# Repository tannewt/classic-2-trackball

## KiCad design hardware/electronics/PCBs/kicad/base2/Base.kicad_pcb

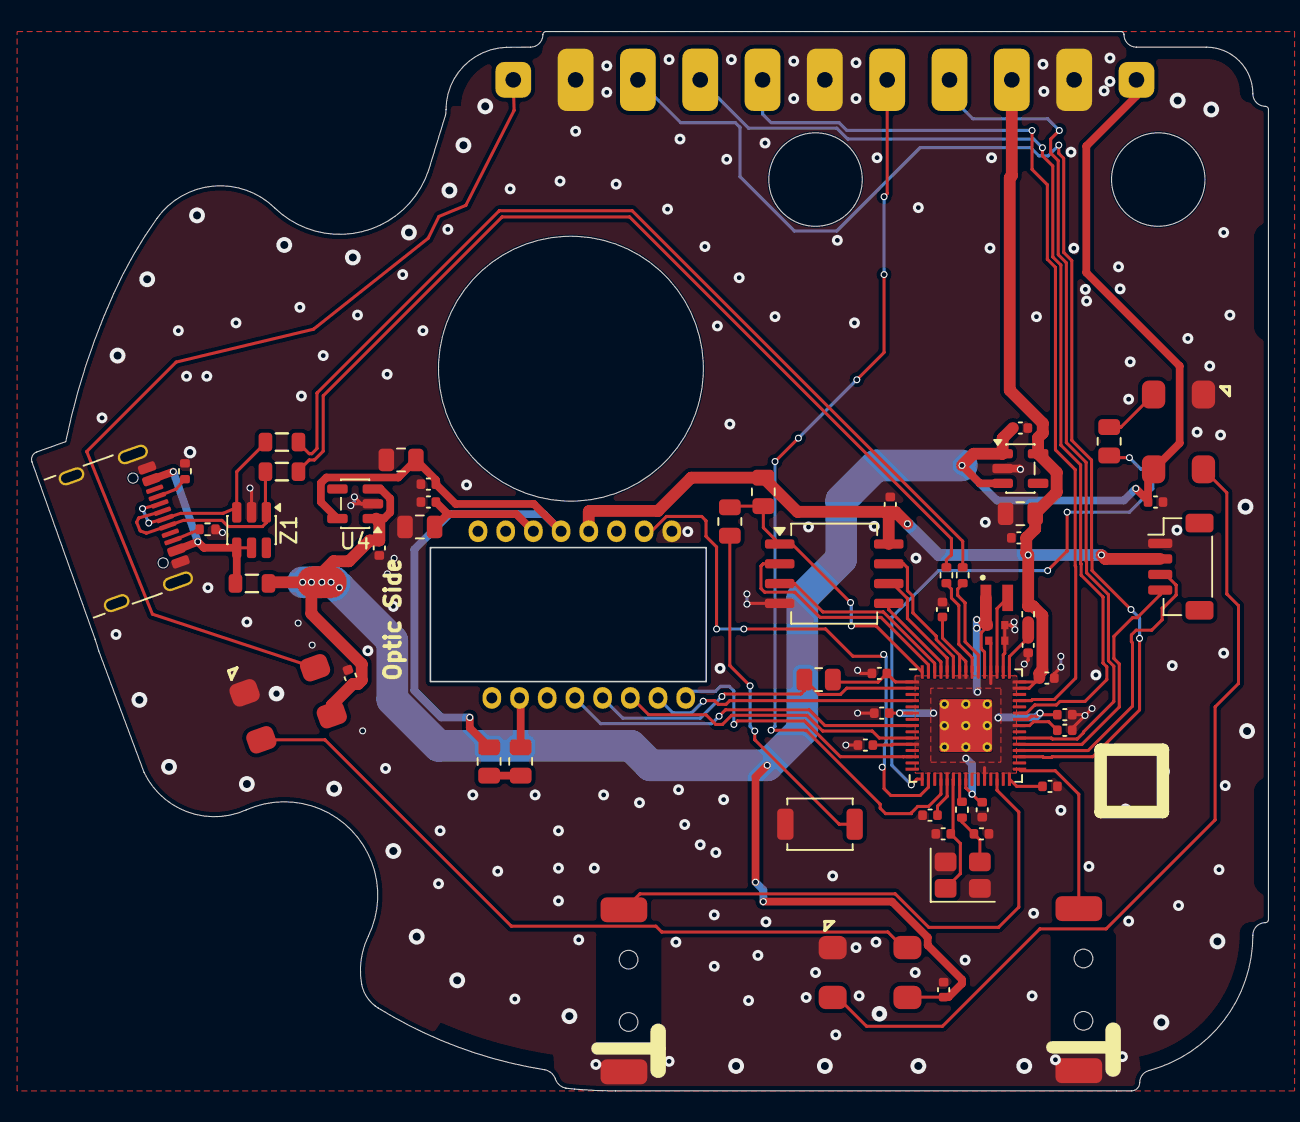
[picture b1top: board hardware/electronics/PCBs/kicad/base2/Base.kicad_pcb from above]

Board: 2 copper layers, 79.4 x 68.0 mm, 69 parts (1 on the bottom side), 49 nets.

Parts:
C1, C11, C15, C20, C23, C24, C25, C29, C30, C31, C32, C33, C34, C35: 100nF; C_0402_1005Metric
C3, C4: 15pF; C_0402_1005Metric
C10, C13, C17: 10uF; C_0805_2012Metric
C12, C14, C16, C18: 1uF; C_0402_1005Metric
C22, C28: 4.7uF; C_0402_1005Metric
C26, C27: 4.7uF; C_0402_1005Metric_small_pads
CJ1, CJ2, CJ3, CJ4, CJ5, CJ6, CJ7, CJ8, CJ9, CJ10, CJ11: PCBJointCastellationJoint; PCBJoint
D1, D3, D5: IN-PI55TATPRPGPB
FB1, FB2, FB3: GZ2012D601TF; FB_0805
J3: USB_C_Receptacle_USB2.0_16P; USB_C_Receptacle_HRO_TYPE-C-31-M-31
J14: Conn_01x04; JST_SH_BM04B-SRSS-TB_1x04-1MP_P1.00mm_Vertical
L1: AOTA-B201610S3R3-101-T; L_pol_2016
R1, R16: 1k; R_0805_2012Metric
R2, R5: 10k; R_0805_2012Metric
R3, R4: 22R; R_0805_2012Metric
R6: 33; R_0402_1005Metric
R7, R8: 27; R_0402_1005Metric
R9: 1k; R_0402_1005Metric
R10, R11: 5.1k; R_0402_1005Metric
SW1, SW2: D2LS-21
SW3: TS-1088-AR02016; SW_SPST_TS-1088-xR020
U1: W25Q16JVSSIQ; SOIC-8_5.3x6.2mm_P1.27mm
U2: PMW3360DM-T2QU
U3: AP2202K-3.3; SOT-23-5
U4: AP2204K-1.8; SOT-23-5
U6: RP2350A; RP2350-QFN-60-1EP_7x7_P0.4mm_EP3.4x3.4mm_ThermalVias
Y1: ABM8-272-T3; Crystal_SMD_3225-4Pin_3.2x2.5mm
Z1: IP4220CZ6,125; SOT-23-6

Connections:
+1V1: C15.1, C22.1, C24.1, C27.1, L1.1, U6.6 (DVDD), U6.23 (DVDD), U6.39 (DVDD), U6.50 (VREG_FB)
+3.3V: C1.2, C13.2, C14.2, C26.1, C29.1, C30.1, C31.1, C32.1, C33.1, C34.1, C35.1, CJ8.1 (1_1), J14.2, R2.1, R5.2, R6.1, U1.8 (VCC), U2.5 (VDDIO), U3.5 (VOUT), U6.1 (IOVDD), U6.11 (IOVDD), U6.20 (IOVDD), U6.26 (RUN), U6.30 (IOVDD), U6.38 (IOVDD), U6.44 (ADC_AVDD), U6.45 (IOVDD), U6.49 (VREG_VIN), U6.53 (USB_OTP_VDD), U6.54 (QSPI_IOVDD)
/LBS/ButtonLittleFinger: SW2.B, U6.31 (GPIO19)
/LBS/ButtonRingFinger: SW1.B, U6.28 (GPIO17)
/LED/LEDData: R16.2, U6.16 (GPIO12)
/LED/LEDDataOut: CJ10.1 (1_1), D5.2 (DOUT)
/LED/V_USB: C12.2, C16.2, C20.2, C23.2, C25.2, CJ11.1 (1_1), D1.1 (VDD), D3.1 (VDD), D5.1 (VDD), FB1.2, U3.1 (VIN), U3.3 (EN), U4.1 (VIN), U4.3 (EN)
/MCU/ButtonLeftClick: CJ6.1 (1_1), U6.19 (GPIO15)
/MCU/ButtonRightClick: CJ7.1 (1_1), U6.36 (GPIO24)
/MCU/ButtonScrollWheel: CJ2.1 (1_1), U6.33 (GPIO21)
/MCU/CS: R1.2, R2.2, U1.1 (~CS), U6.60 (~QSPI_SS)
/MCU/D+: R8.2, U6.52 (USB_DP)
/MCU/D-: R7.2, U6.51 (USB_DM)
/MCU/MISO: R5.1, U2.12 (MISO), U6.2 (GPIO0)
/MCU/MOSI: U2.11 (MOSI), U6.10 (GPIO7)
/MCU/MOTION: U2.9 (MOTION), U6.13 (GPIO9)
/MCU/SCLK: U2.10 (SCLK), U6.4 (GPIO2)
/MCU/ScrollWheelOpto0: CJ3.1 (1_1), U6.40 (GPIO26/ADC0)
/MCU/ScrollWheelOpto1: CJ4.1 (1_1), U6.42 (GPIO28/ADC2)
/MCU/VREG_AVDD: C28.1, R6.2, U6.46 (VREG_AVDD)
/MCU/VREG_LX: L1.2, U6.48 (VREG_LX)
/MCU/XIN: C3.1, U6.21 (XIN), Y1.1
/MCU/XOUT: R9.1, U6.22 (XOUT)
/MCU/~CS: U2.13 (~CS), U6.8 (GPIO5)
/MCU/~RESET: U2.7 (~RESET), U6.17 (GPIO13)
/MOS/1V8: C17.2, C18.2, R3.2, U2.4 (VDD), U4.5 (VOUT)
/SCL: J14.4, U6.35 (GPIO23)
/SDA: J14.3, U6.34 (GPIO22)
/USB/USB_D+: FB3.2, R8.1
/USB/USB_D-: FB2.2, R7.1
GND: C1.1, C3.2, C4.2, C10.1, C11.1, C12.1, C13.1, C14.1, C15.2, C16.1, C17.1, C18.1, C20.1, C22.2, C23.1, C24.2, C25.1, C26.2, C27.2, C28.2, C29.2, C30.2, C31.2, C32.2, C33.2, C34.2, C35.2, CJ1.1 (1_1), CJ5.1 (1_1), CJ9.1 (1_1), D1.3 (VSS), D3.3 (VSS), D5.3 (VSS), J3.A1 (GND), J3.A12 (GND), J3.B1 (GND), J3.B12 (GND), J3.SH (SHIELD), J14.1, R10.2, R11.2, SW1.A, SW2.A, SW3.1, U1.4 (GND), U2.8 (GND), U3.2 (GND), U4.2 (GND), U6.47 (VREG_PGND), U6.61 (GND), Y1.2, Y1.4, Z1.2
unnamed: C4.1, R9.2, Y1.3
unnamed: D1.4 (DIN), R16.1
unnamed: D1.2 (DOUT), D3.4 (DIN)
unnamed: D3.2 (DOUT), D5.4 (DIN)
unnamed: FB1.1, J3.A4 (VBUS), J3.A9 (VBUS), J3.B4 (VBUS), J3.B9 (VBUS), Z1.4, Z1.5
unnamed: FB2.1, J3.A7 (D-), J3.B7 (D-), Z1.3
unnamed: FB3.1, J3.A6 (D+), J3.B6 (D+), Z1.1
unnamed: J3.A5 (CC1), R10.1
unnamed: J3.B5 (CC2), R11.1
unnamed: R1.1, SW3.2
unnamed: R3.1, R4.2
unnamed: U1.6 (CLK), U6.56 (QSPI_SCLK)
unnamed: U1.5 (DI_(IO0)), U6.57 (QSPI_SD0)
unnamed: U1.2 (DO_(IO1)), U6.59 (QSPI_SD1)
unnamed: U1.7 (~HOLD_or_~RESET_(IO3)), U6.55 (QSPI_SD3)
unnamed: U1.3 (~WP_(IO2)), U6.58 (QSPI_SD2)
unnamed: R4.1, U2.15 (LED_P)
unnamed: C10.2, C11.2, U2.3 (VDDPIX)

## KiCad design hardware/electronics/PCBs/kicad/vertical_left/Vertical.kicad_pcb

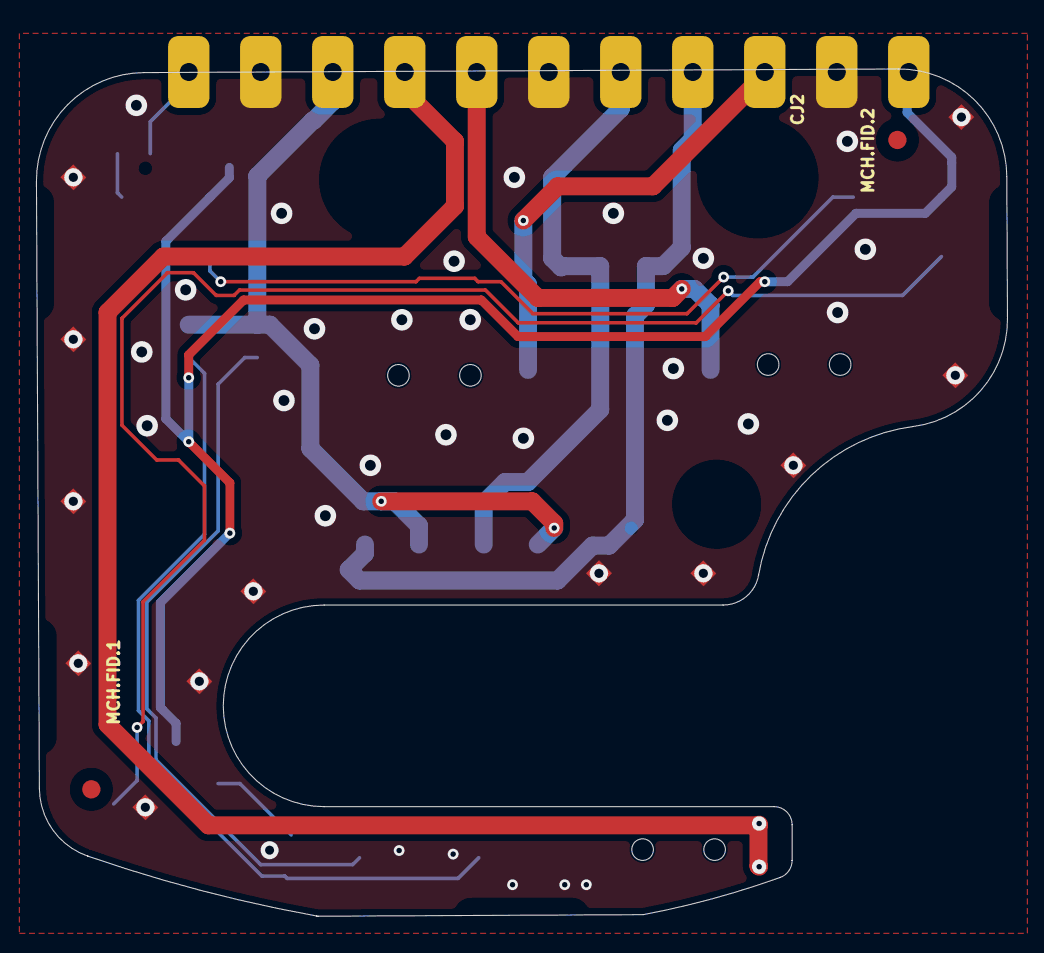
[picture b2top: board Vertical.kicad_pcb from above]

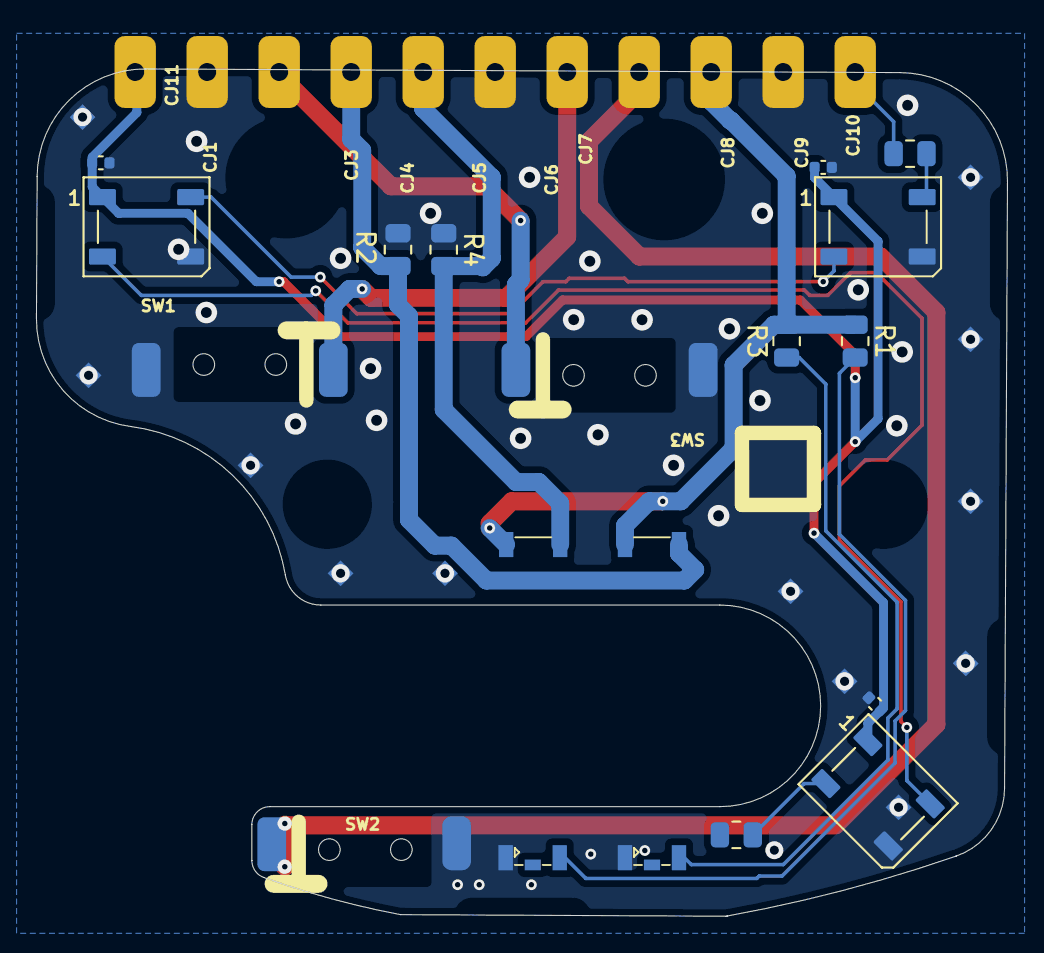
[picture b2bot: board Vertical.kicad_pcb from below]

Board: 2 copper layers, 53.9 x 47.1 mm, 46 parts (19 on the bottom side), 15 nets.

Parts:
C20, C23, C25: 100nF; C_0402_1005Metric
CJ1, CJ2, CJ3, CJ4, CJ5, CJ6, CJ7, CJ8, CJ9, CJ10, CJ11: PCBJointCastellationJoint; PCBJoint
D1, D2: IR12-21C/TR8 or VSMB10940; IR12-21CTR8
D3, D4, D5: IN-PI55TATPRPGPB; LED_WS2812B_PLCC4_5.0x5.0mm_P3.2mm
MCH.FID.1, MCH.FID.2: IPC-7351 Fiducial 1mm; FIDUCIAL_1.5
MCH.FID.3, MCH.FID.4: 1mm Fiducial for OpenPNP; FIDUCIAL-NEW
MCH.SP.1, MCH.SP.2, MCH.SP.3, MCH.SP.4, MCH.SP.5, MCH.SP.6, MCH.SP.7, MCH.SP.8, MCH.SP.9, MCH.SP.10, MCH.SP.11, MCH.SP.12: Spark Gap; SparkGap
Q1, Q2: PT26-51B/TR8; PT26-51B-TR8
R1, R3: 100; R_0805_2012Metric
R2, R4, R16, R17: 1k; R_0805_2012Metric
SW1, SW2, SW3: D2LS-21

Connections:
/BBS/ButtonLeftClick: CJ6.1 (1_1), SW1.A
/BBS/ButtonRightClick: CJ7.1 (1_1), SW2.A
/LEDs/LEDData: CJ10.1 (1_1), R16.2
/LEDs/V_USB: C20.2, C23.2, C25.2, CJ11.1 (1_1), D3.1 (VDD), D4.1 (VDD), D5.1 (VDD)
/SCW/3V3: CJ8.1 (1_1), Q1.2 (C), Q2.2 (C), R1.1, R3.2
/SCW/ButtonScrollWheel: CJ2.1 (1_1), SW3.A
/SCW/ScrollWheelOpto0: CJ3.1 (1_1), Q1.1 (E), R2.2
/SCW/ScrollWheelOpto1: CJ4.1 (1_1), Q2.1 (E), R4.2
GND: C20.1, C23.1, C25.1, CJ1.1 (1_1), CJ5.1 (1_1), CJ9.1 (1_1), D1.2 (C), D2.2 (C), D3.3 (VSS), D4.3 (VSS), D5.3 (VSS), MCH.SP.1.1, MCH.SP.2.1, MCH.SP.3.1, MCH.SP.4.1, MCH.SP.5.1, MCH.SP.6.1, MCH.SP.7.1, MCH.SP.8.1, MCH.SP.9.1, MCH.SP.10.1, MCH.SP.11.1, MCH.SP.12.1, R2.1, R4.1, SW1.B, SW2.B, SW3.B
unnamed: D1.1 (A), R1.2
unnamed: D2.1 (A), R3.1
unnamed: D3.4 (DIN), R16.1
unnamed: D3.2 (DOUT), D4.4 (DIN)
unnamed: D4.2 (DOUT), D5.4 (DIN)
unnamed: D5.2 (DOUT), R17.1 (1_1)

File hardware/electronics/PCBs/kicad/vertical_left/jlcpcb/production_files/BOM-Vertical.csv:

Comment,Designator,Footprint,LCSC,Quantity
100,"R1,R3",R_0805_2012Metric,C17408,2
100nF,"C20,C23,C25",C_0402_1005Metric,C1525,3
1k,"R16,R17,R2,R4",R_0805_2012Metric,C17513,4
D2LS-21,"SW1,SW2,SW3",D2LS-21,C3823622,3
IN-PI55TATPRPGPB,"D3,D4,D5",LED_WS2812B_PLCC4_5.0x5.0mm_P3.2mm,C26167850,3
IR12-21C/TR8 or VSMB10940,"D1,D2",IR12-21CTR8,C53672,2
PT26-51B/TR8,"Q1,Q2",PT26-51B-TR8,C55976,2

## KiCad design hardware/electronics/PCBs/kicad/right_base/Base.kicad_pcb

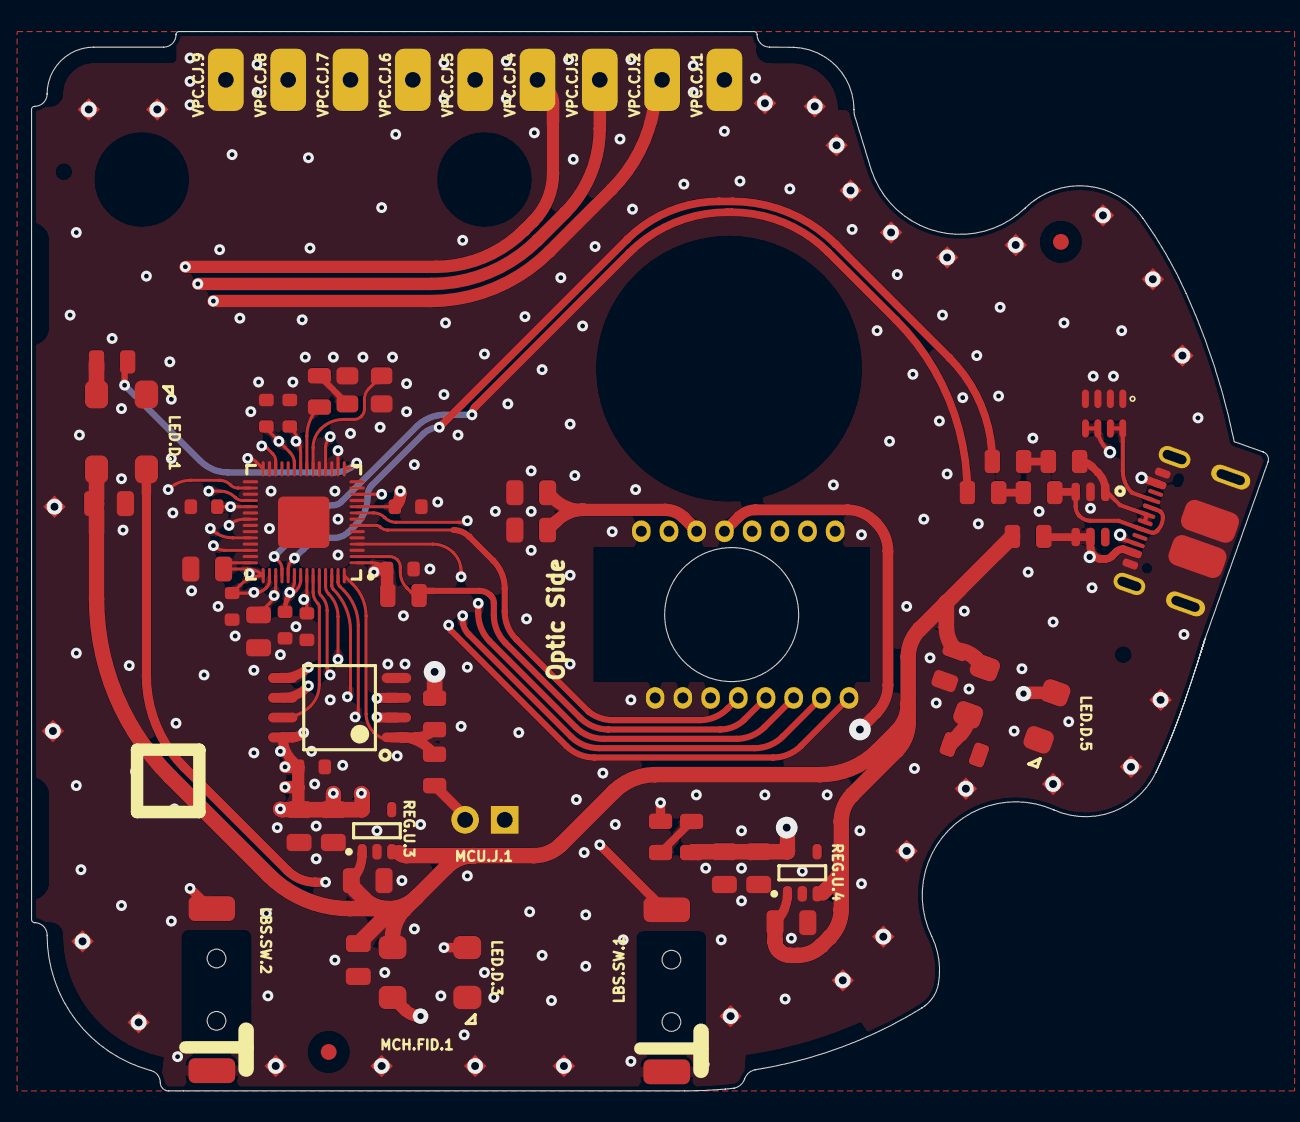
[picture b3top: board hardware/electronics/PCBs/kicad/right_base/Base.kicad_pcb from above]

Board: 4 copper layers, 79.4 x 68.0 mm, 91 parts (1 on the bottom side), 45 nets.

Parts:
LBS.SW.1, LBS.SW.2: D2LS-21
LED.C.20, LED.C.23, LED.C.25: 0805; 0805 - TALL
LED.D.1, LED.D.3, LED.D.5: IN-PI55TATPRPGPB
LED.R.16, LED.R.18: 0805
MCH.FID.1, MCH.FID.2: IPC-7351 Fiducial 1mm; FIDUCIAL_1.5
MCH.FID.3, MCH.FID.4: 1mm Fiducial for OpenPNP; FIDUCIAL-NEW
MCH.SP.1, MCH.SP.2, MCH.SP.3, MCH.SP.4, MCH.SP.5, MCH.SP.6, MCH.SP.7, MCH.SP.8, MCH.SP.9, MCH.SP.10, MCH.SP.11, MCH.SP.12, MCH.SP.13, MCH.SP.14, MCH.SP.15, MCH.SP.16, MCH.SP.17, MCH.SP.18, MCH.SP.19, MCH.SP.20, MCH.SP.21, MCH.SP.22, MCH.SP.23, MCH.SP.24, MCH.SP.25, MCH.SP.26, MCH.SP.27, MCH.SP.28: Spark Gap; SparkGap
MCU.C.1, MCU.C.3, MCU.C.4, MCU.C.5, MCU.C.6, MCU.C.7, MCU.C.8, MCU.C.19, MCU.C.21: 0603 X5R; 0603 capacitor - CAPC1608X06N
MCU.C.2, MCU.C.9: 0805 X5R; 0805 - TALL
MCU.J.1: HEADER2; 2x1
MCU.R.1, MCU.R.2, MCU.R.6: 0805
MCU.U.1: W25Q16JVSSIQ; W25Q128JVS - SOIC127P790X216-8M
MCU.U.5: RP2040; RP2040 - QFN40P700X700X90_HS-57M
MCU.Y.1: RH100-12.000-16-3030
MOS.C.10, MOS.C.11: 0805; 0805 - TALL
MOS.R.3, MOS.R.4, MOS.R.5: 0805
MOS.U.2: PMW3360DM-T2QU
REG.C.12, REG.C.13, REG.C.14, REG.C.16, REG.C.17, REG.C.18: 0805; 0805 - TALL
REG.U.3: AP2202K-3.3; AP2202 - SOT95P270X145-5N
REG.U.4: AP2204K-1.8; AP2202 - SOT95P270X145-5N
USB.FB.1, USB.FB.2, USB.FB.3: ACML-0805-601-T; 0805
USB.J.2: DX07S016JA1R1500
USB.R.7, USB.R.8: 0805
USB.Ra.1: 1206 Quad; 4x 10k 1% - CAC-80P320X160-8M
USB.Z.1: IP4220CZ6,125; PESD3V3S4UD - SOT95P275X110-6N
VPC.CJ.1, VPC.CJ.2, VPC.CJ.3, VPC.CJ.4, VPC.CJ.5, VPC.CJ.6, VPC.CJ.7, VPC.CJ.8, VPC.CJ.9: PCBJointCastellationJoint; PCBJoint

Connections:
1V1: MCU.C.9.2, MCU.C.19.2, MCU.C.21.2, MCU.U.5.23, MCU.U.5.45, MCU.U.5.50
1V8: MOS.R.3.2, MOS.U.2.4, REG.C.17.2, REG.C.18.2, REG.U.4.5
3V3: MCU.C.1.2, MCU.C.2.2, MCU.C.3.2, MCU.C.4.2, MCU.C.5.2, MCU.C.6.2, MCU.C.7.2, MCU.C.8.2, MCU.R.2.1, MCU.U.1.8, MCU.U.5.1, MCU.U.5.10, MCU.U.5.22, MCU.U.5.26, MCU.U.5.33, MCU.U.5.42, MCU.U.5.43, MCU.U.5.44, MCU.U.5.48, MCU.U.5.49, MOS.R.5.2, MOS.U.2.5, REG.C.13.2, REG.C.14.2, REG.U.3.5, VPC.CJ.8.1
GND: LBS.SW.1.A, LBS.SW.2.A, LED.C.20.1, LED.C.23.1, LED.C.25.1, LED.D.1.3, LED.D.3.3, LED.D.5.3, MCH.SP.1.1, MCH.SP.2.1, MCH.SP.3.1, MCH.SP.4.1, MCH.SP.5.1, MCH.SP.6.1, MCH.SP.7.1, MCH.SP.8.1, MCH.SP.9.1, MCH.SP.10.1, MCH.SP.11.1, MCH.SP.12.1, MCH.SP.13.1, MCH.SP.14.1, MCH.SP.15.1, MCH.SP.16.1, MCH.SP.17.1, MCH.SP.18.1, MCH.SP.19.1, MCH.SP.20.1, MCH.SP.21.1, MCH.SP.22.1, MCH.SP.23.1, MCH.SP.24.1, MCH.SP.25.1, MCH.SP.26.1, MCH.SP.27.1, MCH.SP.28.1, MCU.C.1.1, MCU.C.2.1, MCU.C.3.1, MCU.C.4.1, MCU.C.5.1, MCU.C.6.1, MCU.C.7.1, MCU.C.8.1, MCU.C.9.1, MCU.C.19.1, MCU.C.21.1, MCU.J.1.1, MCU.U.1.4, MCU.U.5.3, MCU.U.5.5, MCU.U.5.6, MCU.U.5.8, MCU.U.5.11, MCU.U.5.13, MCU.U.5.14, MCU.U.5.17, MCU.U.5.19, MCU.U.5.27, MCU.U.5.29, MCU.U.5.31, MCU.U.5.34, MCU.U.5.36, MCU.U.5.37, MCU.U.5.39, MCU.U.5.41, MCU.U.5.57, MCU.Y.1.2, MCU.Y.1.4, MOS.C.10.1, MOS.C.11.1, MOS.U.2.8, REG.C.12.1, REG.C.13.1, REG.C.14.1, REG.C.16.1, REG.C.17.1, REG.C.18.1, REG.U.3.2, REG.U.4.2, USB.J.2.1, USB.J.2.12, USB.J.2.SHELL, USB.Ra.1.1, USB.Ra.1.2, USB.Ra.1.3, USB.Ra.1.4, USB.Z.1.2, VPC.CJ.1.1, VPC.CJ.5.1, VPC.CJ.9.1
LEDData: LED.R.16.2, MCU.U.5.15
NetLBS.SW.1_B: LBS.SW.1.B, MCU.U.5.28
NetLBS.SW.2_B: LBS.SW.2.B, MCU.U.5.30
NetLED.D.1_2: LED.D.1.2, LED.D.3.4
NetLED.D.1_4: LED.D.1.4, LED.R.16.1
NetLED.D.3_2: LED.D.3.2, LED.D.5.4
NetLED.D.5_2: LED.D.5.2, LED.R.18.2
NetMCU.J.1_2: MCU.J.1.2, MCU.R.1.1
NetMCU.R.1_2: MCU.R.1.2, MCU.R.2.2, MCU.U.1.1, MCU.U.5.56
NetMCU.R.6_1: MCU.R.6.1, MCU.U.5.21
NetMCU.R.6_2: MCU.R.6.2, MCU.Y.1.3
NetMCU.U.1_2: MCU.U.1.2, MCU.U.5.55
NetMCU.U.1_3: MCU.U.1.3, MCU.U.5.54
NetMCU.U.1_5: MCU.U.1.5, MCU.U.5.53
NetMCU.U.1_6: MCU.U.1.6, MCU.U.5.52
NetMCU.U.1_7: MCU.U.1.7, MCU.U.5.51
NetMCU.U.5_2: MCU.U.5.2, MOS.R.5.1, MOS.U.2.12
NetMCU.U.5_4: MCU.U.5.4, MOS.U.2.10
NetMCU.U.5_7: MCU.U.5.7, MOS.U.2.13
NetMCU.U.5_9: MCU.U.5.9, MOS.U.2.11
NetMCU.U.5_12: MCU.U.5.12, MOS.U.2.9
NetMCU.U.5_16: MCU.U.5.16, MOS.U.2.7
NetMCU.U.5_18: MCU.U.5.18, VPC.CJ.6.1
NetMCU.U.5_20: MCU.U.5.20, MCU.Y.1.1
NetMCU.U.5_32: MCU.U.5.32, VPC.CJ.2.1
NetMCU.U.5_35: MCU.U.5.35, VPC.CJ.7.1
NetMCU.U.5_38: MCU.U.5.38, VPC.CJ.3.1
NetMCU.U.5_40: MCU.U.5.40, VPC.CJ.4.1
NetMCU.U.5_46: MCU.U.5.46, USB.R.7.2
NetMCU.U.5_47: MCU.U.5.47, USB.R.8.2
NetMOS.C.10_2: MOS.C.10.2, MOS.C.11.2, MOS.U.2.3
NetMOS.R.3_1: MOS.R.3.1, MOS.R.4.2
NetMOS.R.4_1: MOS.R.4.1, MOS.U.2.15
NetUSB.FB.1_1: USB.FB.1.1, USB.J.2.2, USB.J.2.11, USB.Z.1.4, USB.Z.1.5
NetUSB.FB.2_1: USB.FB.2.1, USB.J.2.5, USB.J.2.8, USB.Z.1.3
NetUSB.FB.2_2: USB.FB.2.2, USB.R.7.1
NetUSB.FB.3_1: USB.FB.3.1, USB.J.2.6, USB.J.2.7, USB.Z.1.1
NetUSB.FB.3_2: USB.FB.3.2, USB.R.8.1
NetUSB.J.2_3: USB.J.2.3, USB.Ra.1.5, USB.Ra.1.6
NetUSB.J.2_9: USB.J.2.9, USB.Ra.1.7, USB.Ra.1.8
V_USB: LED.C.20.2, LED.C.23.2, LED.C.25.2, LED.D.1.1, LED.D.3.1, LED.D.5.1, REG.C.12.2, REG.C.16.2, REG.U.3.1, REG.U.3.3, REG.U.4.1, REG.U.4.3, USB.FB.1.2

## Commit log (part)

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2026-03-19 Working on left
2026-03-19 Kicad nightly import
2026-06-08 add vertical
2026-06-08 Vertical portion flipped
2026-06-09 Getting parts right
2026-06-09 To order

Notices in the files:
hardware/electronics/PCBs/kicad/base2/Base.kicad_pcb:
Licensed under the
CERN-OHL-S v2
Copyright Ploopy
Copyright Scott Shawcroft
hardware/electronics/PCBs/kicad/vertical_left/Vertical.kicad_pcb:
the CERN-OHL-S v2
Copyright Ploopy 2024
